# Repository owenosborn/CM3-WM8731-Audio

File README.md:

# CM3-WM8731-Audio
A basic audio board based on Raspberry Pi CM3 and WM8731 audio codec. Eagle PCB files.

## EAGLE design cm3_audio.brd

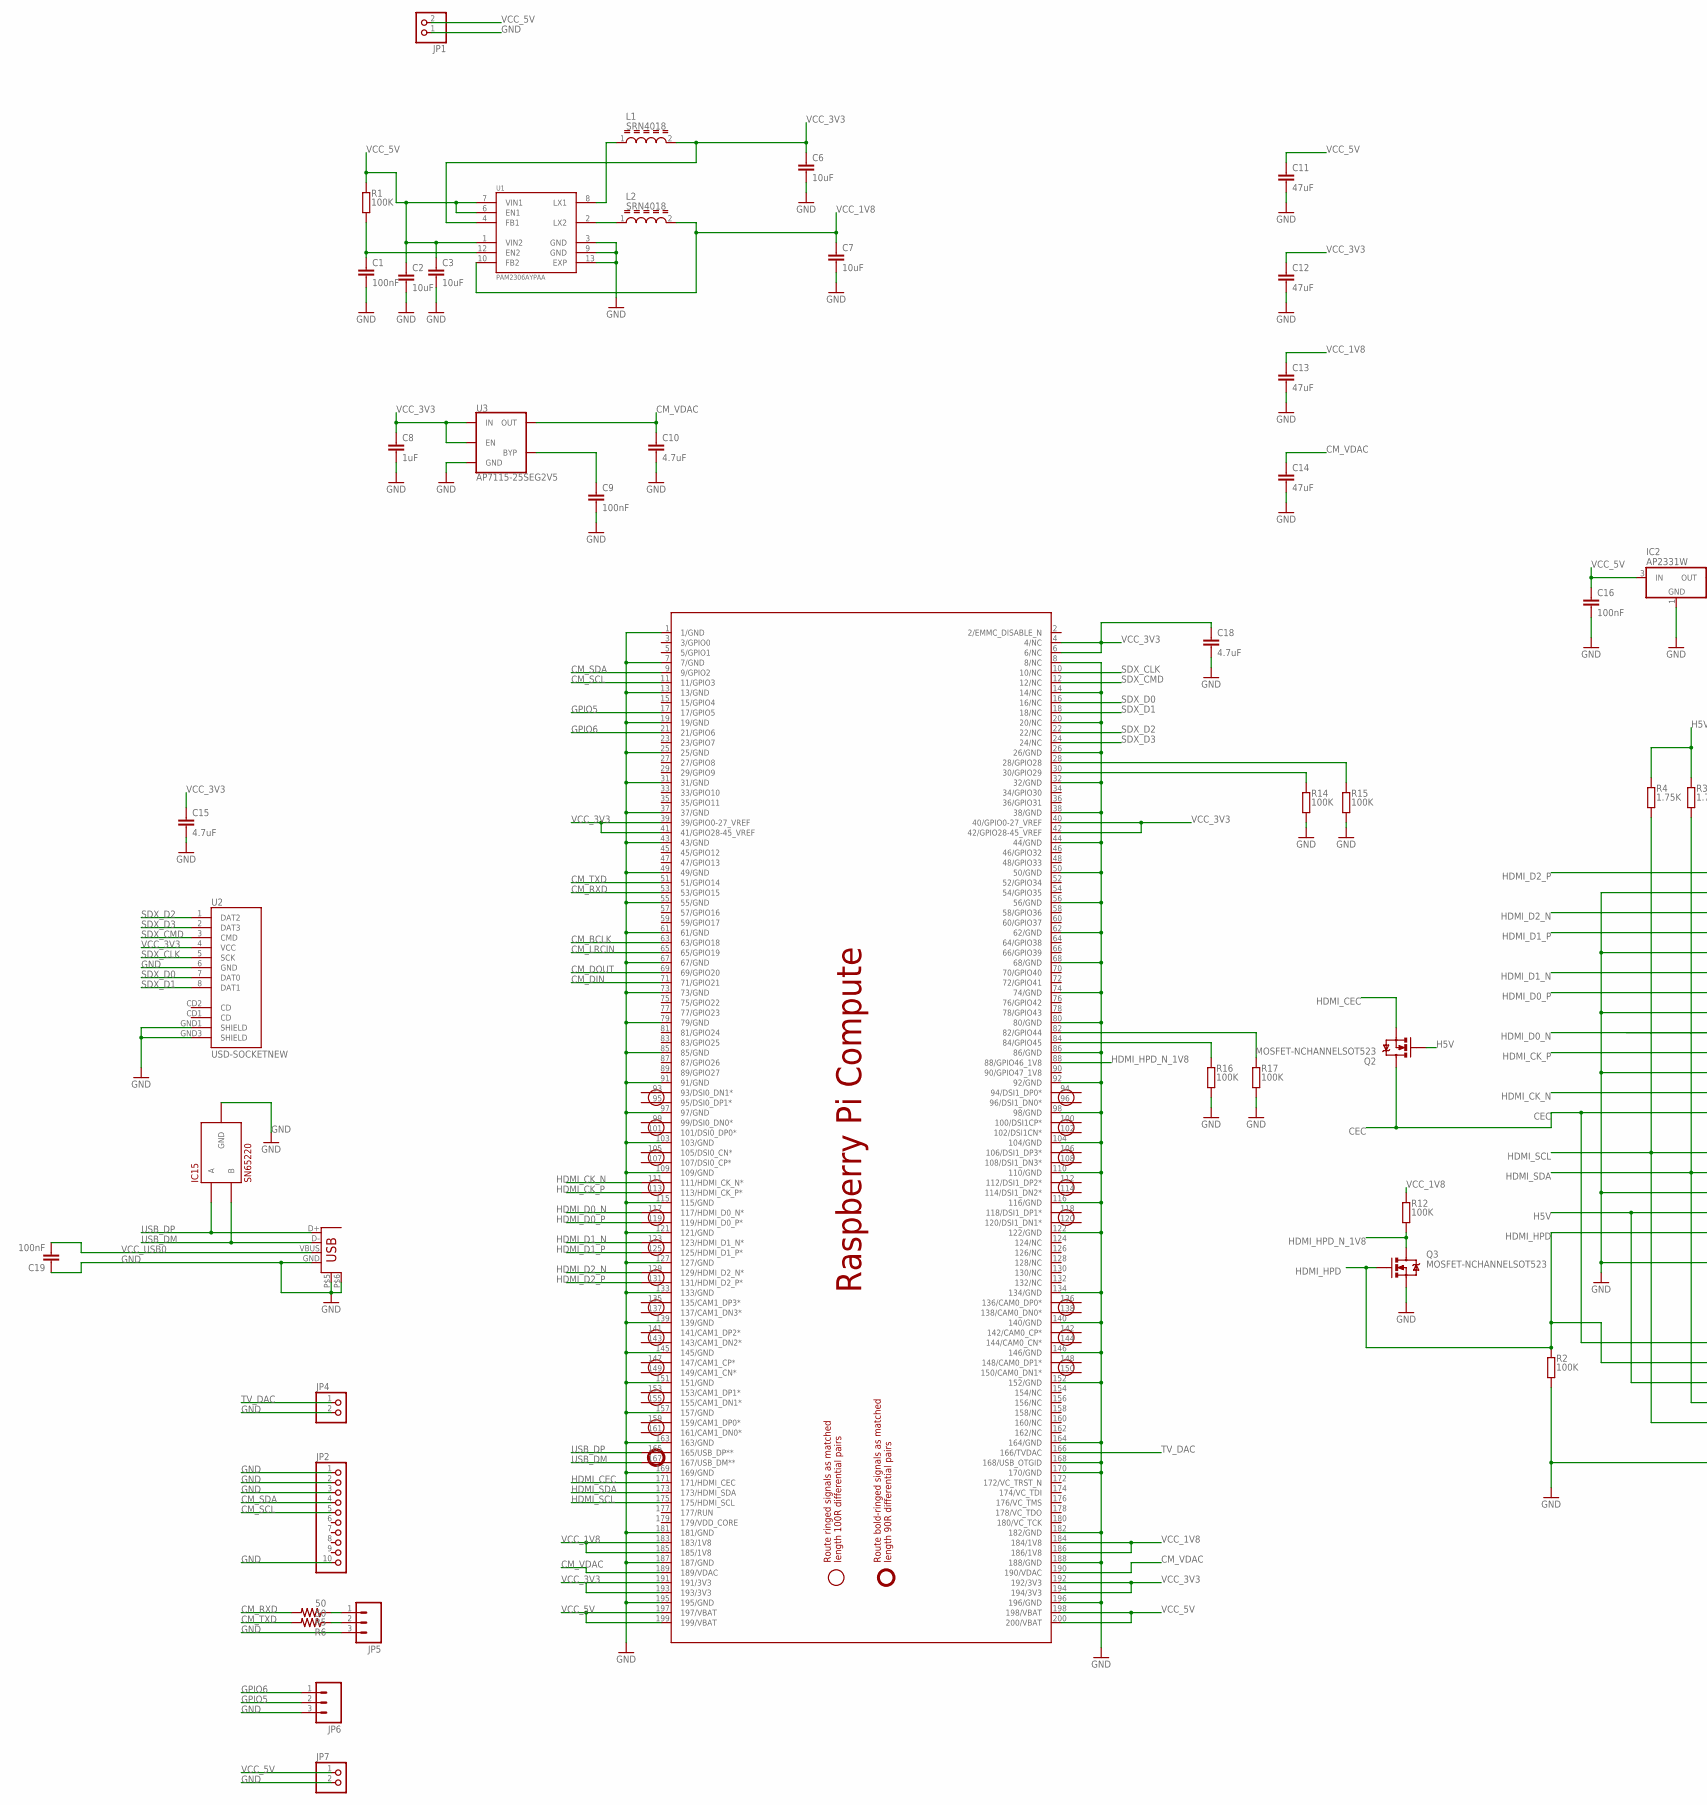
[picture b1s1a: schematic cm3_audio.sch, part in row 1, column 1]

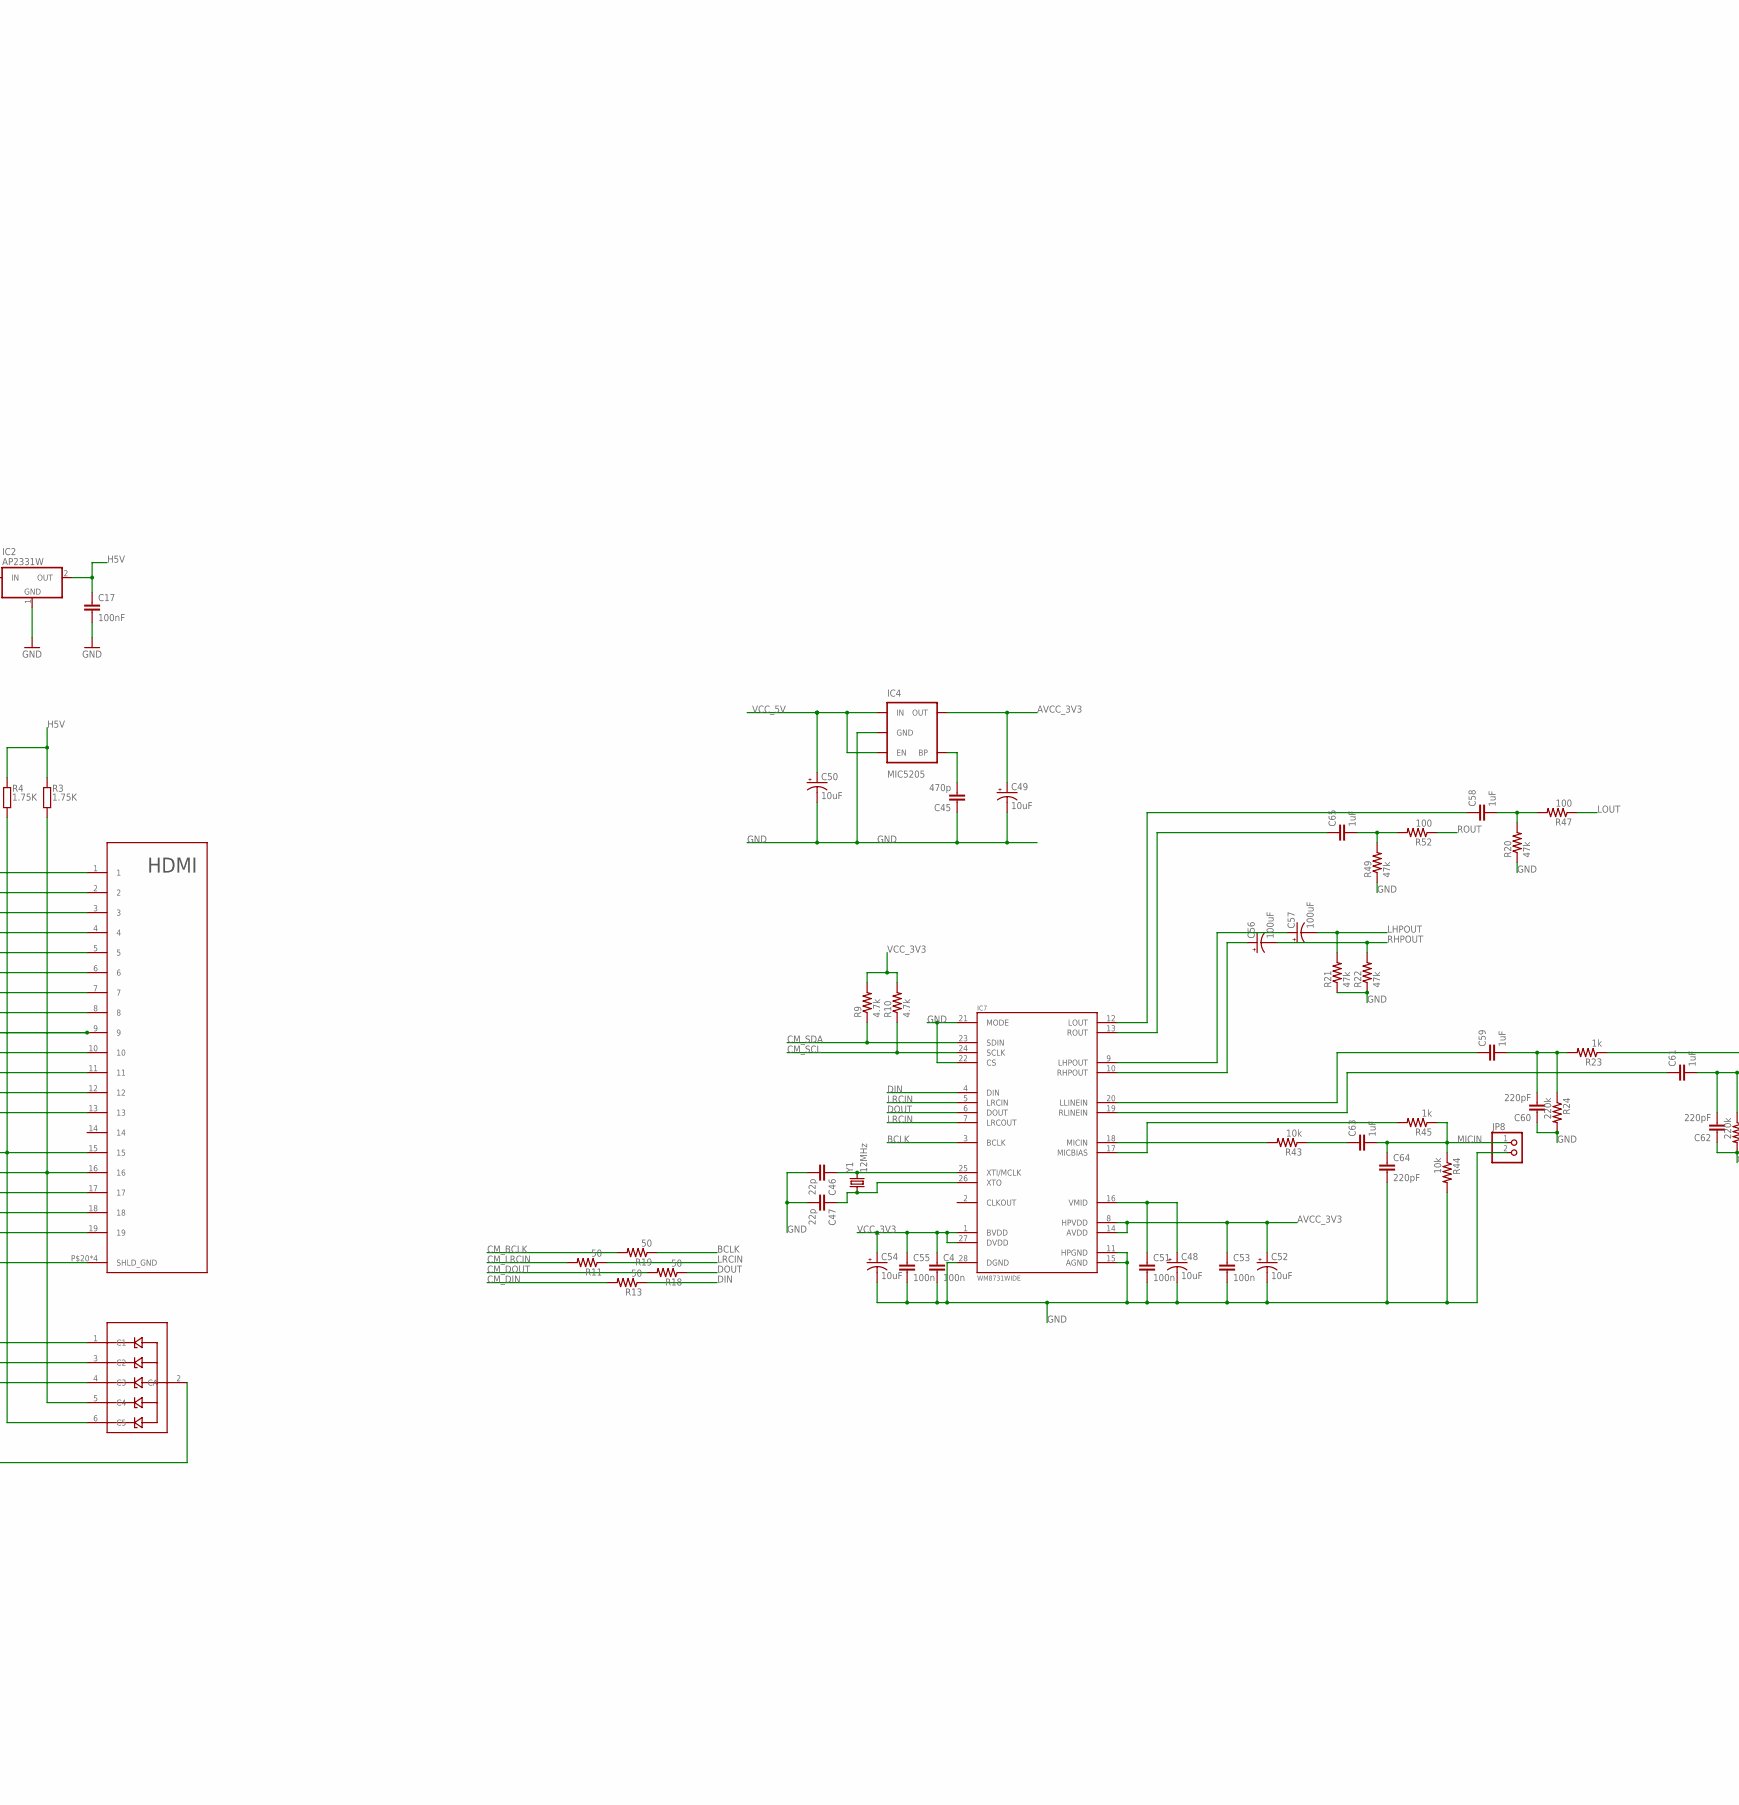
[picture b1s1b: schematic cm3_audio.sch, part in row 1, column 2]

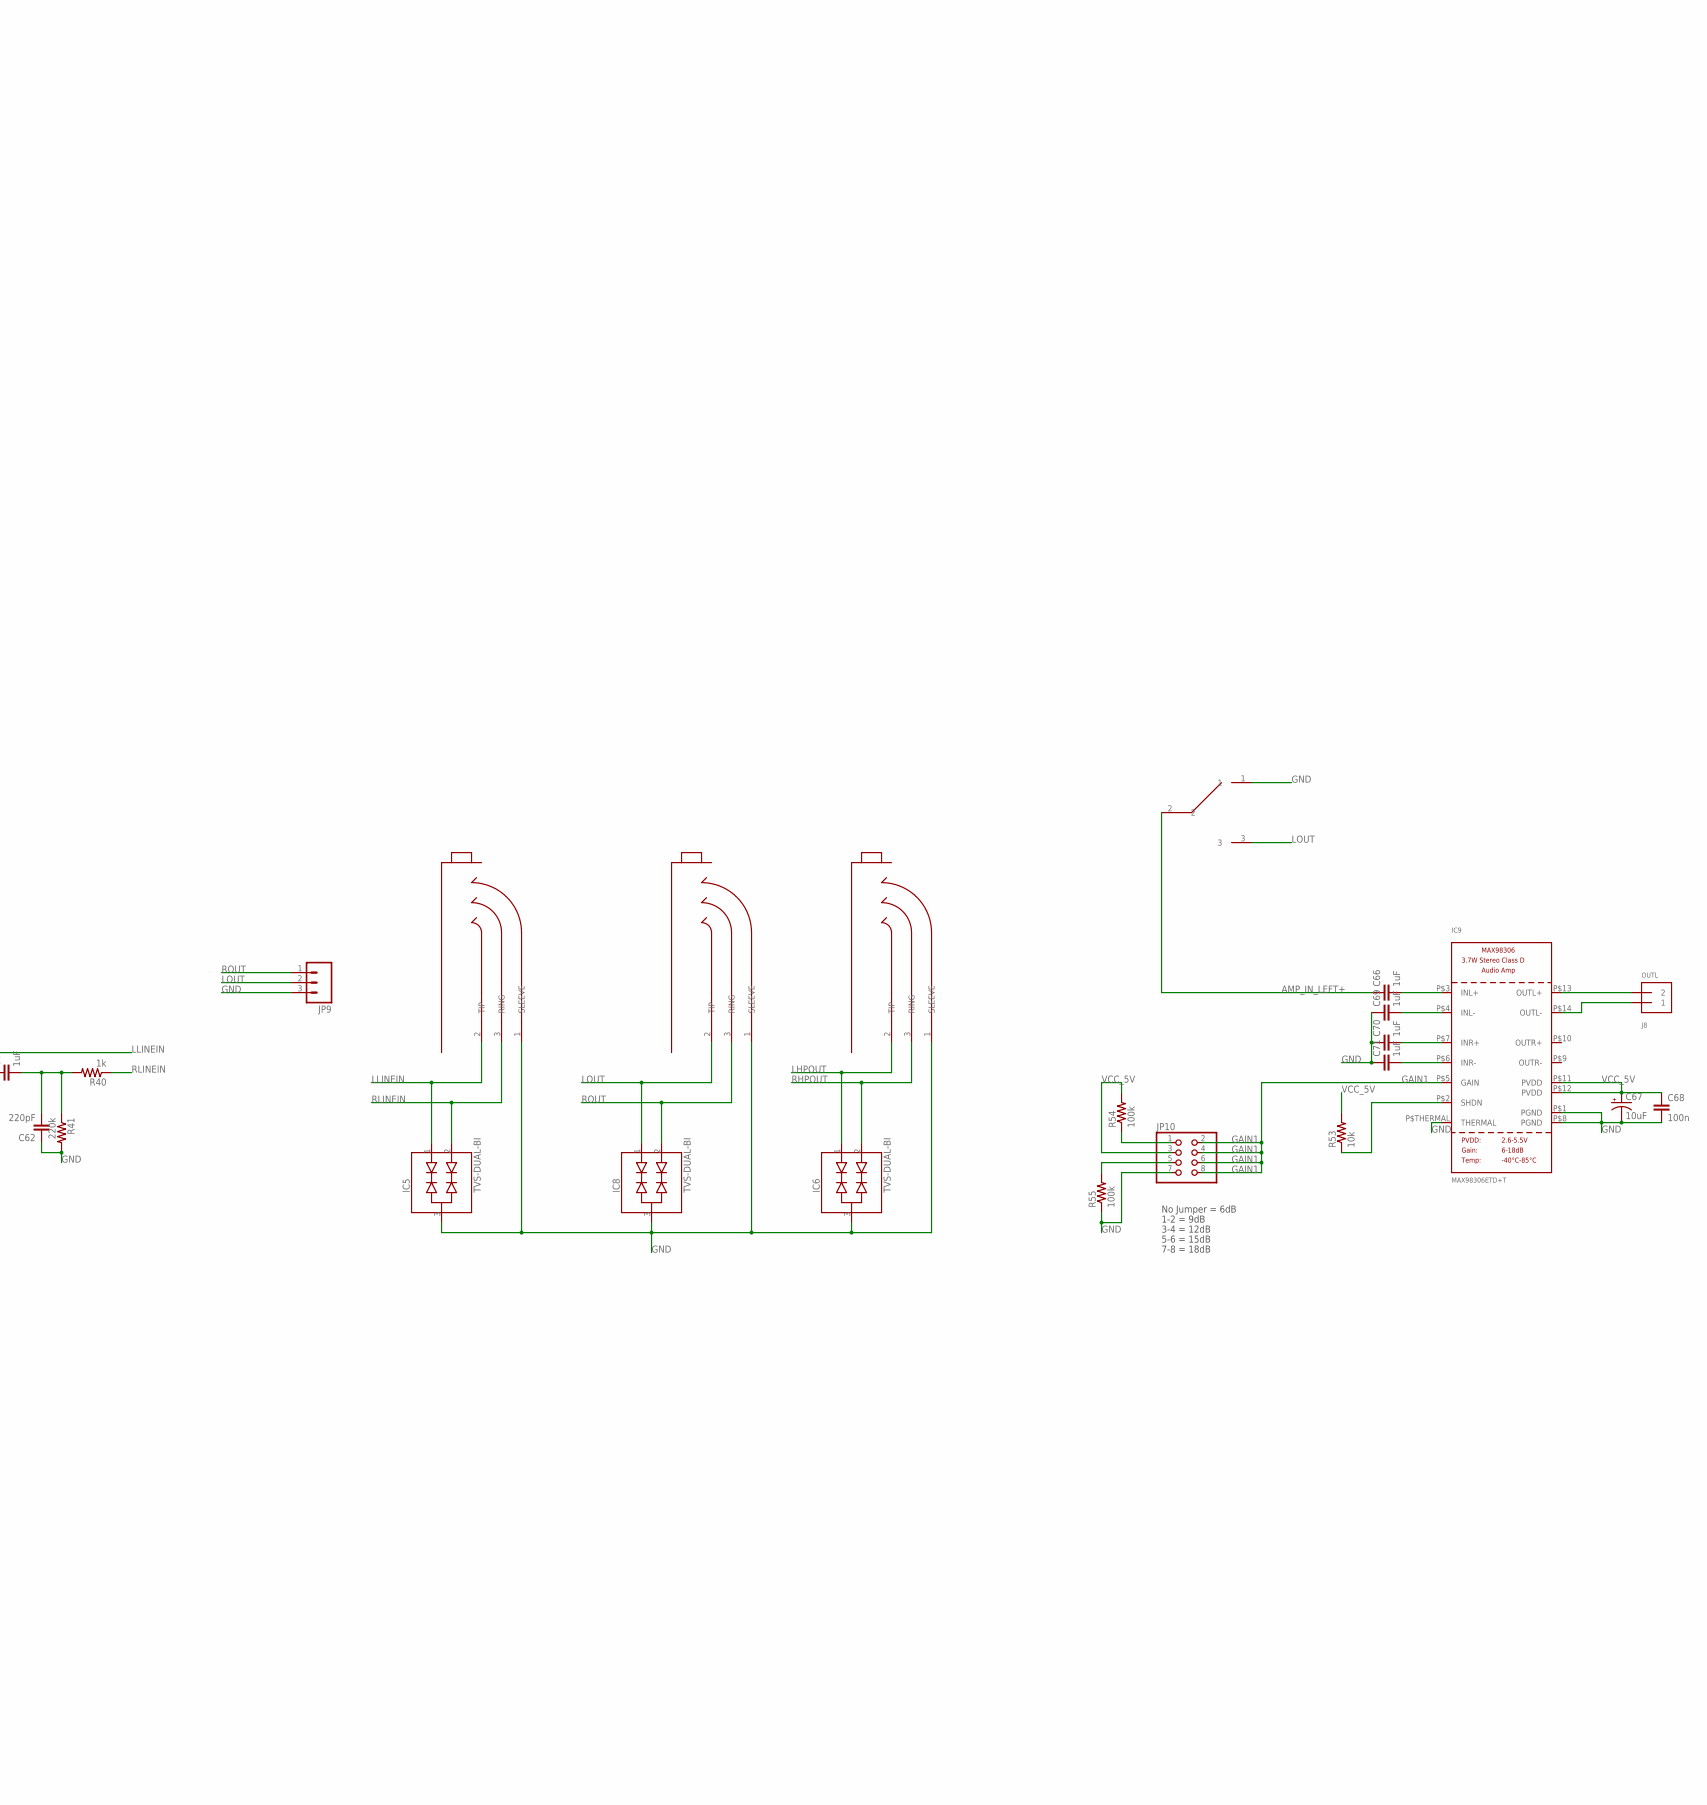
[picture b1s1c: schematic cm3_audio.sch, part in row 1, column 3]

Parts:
C1, C9, C16, C17: 100nF; C0603
C2, C3, C6, C7: 10uF; C0805
C4, C51, C53, C55, C68: 100n; 0603-CAP
C8: 1uF; C0603
C10, C15: 4.7uF; C0603
C11, C12, C13, C14: 47uF; C3216
C18: 4.7uF; C1608
C19: 100nF; 0603-CAP
C45: 470p; 0603-CAP
C46, C47: 22p; 0603-CAP
C48, C49, C50, C52, C54, C67: 10uF; PANASONIC_B
C56, C57: 100uF; PANASONIC_D
C58, C59, C61, C63, C65, C66, C69, C70, C71: 1uF; 0603-CAP
C60, C62, C64: 220pF; 0603-CAP
IC1: PESD3V3L5UYSOT363; SOT363-INFINION
IC2: AP2331W; SOT23
IC4: MIC5205; SPARKFUN-3-2-07_SOT23-5
IC5, IC6, IC8: TVS-DUAL-BI; SOT23
IC7: WM8731WIDE; SSOP28DB
IC9: MAX98306ETD+T; TDFN14_3X3MM
IC15: SN65220; SOT23-6L
J1, J6, J7: STEREO_HEADPHONE_NO_SWITCH; 3.5MM-JACK-SJ1-351X-SMT
J8: OUTL; TERMBLOCK_1X2-3.5MM
JP1, JP4, JP7, JP8: PINHD-1X2; 1X02
JP2: PINHD-1X10; 1X10
JP3: USB-A; USB-A-S-NOSILK-FEMALE
JP5, JP6: M03LOCK_LONGPADS; 1X03_LOCK_LONGPADS
JP9: M03LONGPADS; 1X03_LONGPADS
JP10: PINHD-2X4; 2X04
L1, L2: SRN4018; INDP4040X180N
Q2, Q3: MOSFET-NCHANNELSOT523; SOT523
R1, R2, R12, R14, R15, R16, R17: 100K; R0603
R3, R4: 1.75K; R0603
R5, R6, R11, R13, R18, R19: 50; 0603-RES
R9, R10: 4.7k; 0603-RES
R20, R21, R22, R49: 47k; 0603-RES
R23, R40, R45: 1k; 0603-RES
R24, R41: 220k; 0603-RES
R43, R44, R53: 10k; 0603-RES
R47, R52: 100; 0603-RES
R54, R55: 100k; 0603-RES
S1: SWITCH_SPDTRA; SLIDE_SWITCH_TE_RA
SODIMM: RPI_COMPUTE
U1: PAM2306AYPAA; SON45P300X300X80-13N
U2: USD-SOCKETNEW; MICRO-SD-SOCKET-PP
U3: AP7115-25SEG2V5; SC70
U4: HDMI
Y1: 12MHz; CRYSTAL-SMD-5X3

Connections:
AMP_IN_LEFT+: C66.1, S1.2
AVCC_3V3: C49.+, C52.+, C53.1, IC4.5 (OUT), IC7.8 (HPVDD), IC7.14 (AVDD)
BCLK: IC7.3 (BCLK), R19.1
CEC: IC1.1 (C1), Q2.3 (D), U4.13
CM_BCLK: R19.2, SODIMM.63 (63/GPIO18)
CM_DIN: R13.2, SODIMM.71 (71/GPIO21)
CM_DOUT: R18.2, SODIMM.69 (69/GPIO20)
CM_LRCIN: R11.2, SODIMM.65 (65/GPIO19)
CM_RXD: R5.2, SODIMM.53 (53/GPIO15)
CM_SCL: IC7.24 (SCLK), JP2.5, R10.1, SODIMM.11 (11/GPIO3)
CM_SDA: IC7.23 (SDIN), JP2.4, R9.1, SODIMM.9 (9/GPIO2)
CM_TXD: R6.2, SODIMM.51 (51/GPIO14)
CM_VDAC: C10.1, C14.1, SODIMM.189 (189/VDAC), SODIMM.190 (190/VDAC), U3.5 (OUT)
DIN: IC7.4 (DIN), R13.1
DOUT: IC7.6 (DOUT), R18.1
GAIN1: IC9.P$5 (GAIN), JP10.2, JP10.4, JP10.6, JP10.8
GND: C1.2, C2.2, C3.2, C4.2, C6.2, C7.2, C8.2, C9.2, C10.2, C11.2, C12.2, C13.2, C14.2, C15.2, C16.2, C17.2, C18.2, C19.1, C45.1, C46.2, C47.2, C48.-, C49.-, C50.-, C51.2, C52.-, C53.2, C54.-, C55.2, C60.1, C62.1, C64.2, C67.-, C68.2, C69.1, C70.1, C71.1, IC1.2 (CA), IC2.1 (GND), IC4.2 (GND), IC5.3 (GND), IC6.3 (GND), IC7.11 (HPGND), IC7.15 (AGND), IC7.21 (MODE), IC7.22 (CS), IC7.28 (DGND), IC8.3 (GND), IC9.P$1 (PGND), IC9.P$8 (PGND), IC9.P$THERMAL (THERMAL), IC15.2 (GND), IC15.5 (GND), J1.1 (SLEEVE), J6.1 (SLEEVE), J7.1 (SLEEVE), JP1.1, JP2.1, JP2.2, JP2.3, JP2.10, JP3.GND, JP3.P$5 (SHIELD1), JP3.P$6 (SHIELD2), JP4.2, JP5.3, JP6.3, JP7.2, JP8.2, JP9.3, JP10.7, Q3.2 (S), R2.1, R14.1, R15.1, R16.1, R17.1, R20.1, R21.1, R22.1, R24.2, R41.2, R44.2, R49.1, R55.1, S1.1, SODIMM.1 (1/GND), SODIMM.7 (7/GND), SODIMM.8 (8/NC), SODIMM.13 (13/GND), SODIMM.14 (14/NC), SODIMM.19 (19/GND), SODIMM.20 (20/NC), SODIMM.25 (25/GND), SODIMM.26 (26/GND), SODIMM.31 (31/GND), SODIMM.32 (32/GND), SODIMM.37 (37/GND), SODIMM.38 (38/GND), SODIMM.43 (43/GND), SODIMM.44 (44/GND), SODIMM.49 (49/GND), SODIMM.50 (50/GND), SODIMM.55 (55/GND), SODIMM.56 (56/GND), SODIMM.61 (61/GND), SODIMM.62 (62/GND), SODIMM.67 (67/GND), SODIMM.68 (68/GND), SODIMM.73 (73/GND), SODIMM.74 (74/GND), SODIMM.79 (79/GND), SODIMM.80 (80/GND), SODIMM.85 (85/GND), SODIMM.86 (86/GND), SODIMM.91 (91/GND), SODIMM.92 (92/GND), SODIMM.97 (97/GND), SODIMM.98 (98/GND), SODIMM.103 (103/GND), SODIMM.104 (104/GND), SODIMM.109 (109/GND), SODIMM.110 (110/GND), SODIMM.115 (115/GND), SODIMM.116 (116/GND), SODIMM.121 (121/GND), SODIMM.122 (122/GND), SODIMM.127 (127/GND), SODIMM.133 (133/GND), SODIMM.134 (134/GND), SODIMM.139 (139/GND), SODIMM.140 (140/GND), SODIMM.145 (145/GND), SODIMM.146 (146/GND), SODIMM.151 (151/GND), SODIMM.152 (152/GND), SODIMM.157 (157/GND), SODIMM.163 (163/GND), SODIMM.164 (164/GND), SODIMM.168 (168/USB_OTGID), SODIMM.169 (169/GND), SODIMM.170 (170/GND), SODIMM.181 (181/GND), SODIMM.182 (182/GND), SODIMM.187 (187/GND), SODIMM.188 (188/GND), SODIMM.195 (195/GND), SODIMM.196 (196/GND), U1.3 (GND), U1.9 (GND), U1.13 (EXP), U2.6 (GND), U2.GND1 (SHIELD), U2.GND3 (SHIELD), U3.2 (GND), U4.2, U4.5, U4.8, U4.11, U4.17, U4.P$20 (SHLD_GND), U4.P$21 (SHLD_GND), U4.P$22 (SHLD_GND), U4.P$23 (SHLD_GND)
GPIO5: JP6.2, SODIMM.17 (17/GPIO5)
GPIO6: JP6.1, SODIMM.21 (21/GPIO6)
H5V: C17.1, IC1.4 (C3), IC2.2 (OUT), Q2.1 (G), R3.2, R4.2, U4.18
HDMI_CEC: Q2.2 (S), SODIMM.171 (171/HDMI_CEC)
HDMI_CK_N: SODIMM.111 (111/HDMI_CK_N*), U4.12
HDMI_CK_P: SODIMM.113 (113/HDMI_CK_P*), U4.10
HDMI_D0_N: SODIMM.117 (117/HDMI_D0_N*), U4.9
HDMI_D0_P: SODIMM.119 (119/HDMI_D0_P*), U4.7
HDMI_D1_N: SODIMM.123 (123/HDMI_D1_N*), U4.6
HDMI_D1_P: SODIMM.125 (125/HDMI_D1_P*), U4.4
HDMI_D2_N: SODIMM.129 (129/HDMI_D2_N*), U4.3
HDMI_D2_P: SODIMM.131 (131/HDMI_D2_P*), U4.1
HDMI_HPD: IC1.3 (C2), Q3.1 (G), R2.2, U4.19
HDMI_HPD_N_1V8: Q3.3 (D), R12.1, SODIMM.88 (88/GPIO46_1V8)
HDMI_SCL: IC1.6 (C5), R4.1, SODIMM.175 (175/HDMI_SCL), U4.15
HDMI_SDA: IC1.5 (C4), R3.1, SODIMM.173 (173/HDMI_SDA), U4.16
LHPOUT: C57.-, IC6.1 (IO1), J1.2 (TIP), R21.2
LLINEIN: IC5.1 (IO1), J7.2 (TIP), R23.1
LOUT: IC8.1 (IO1), J6.2 (TIP), JP9.2, R47.1, S1.3
LOUT-1: IC9.P$14 (OUTL-), J8.1
LRCIN: IC7.5 (LRCIN), IC7.7 (LRCOUT), R11.1
MICIN: C63.2, C64.1, JP8.1, R44.1, R45.1
unnamed: L1.1, U1.8 (LX1)
unnamed: C1.1, R1.1, U1.12 (EN2)
unnamed: JP5.1, R5.1
unnamed: JP5.2, R6.1
unnamed: L2.1, U1.2 (LX2)
unnamed: C9.1, U3.4 (BYP)
unnamed: R16.2, SODIMM.84 (84/GPIO45)
unnamed: R15.2, SODIMM.28 (28/GPIO28)
unnamed: R14.2, SODIMM.30 (30/GPIO29)
unnamed: R17.2, SODIMM.82 (82/GPIO44)
unnamed: C45.2, IC4.4 (BP)
unnamed: C46.1, IC7.25 (XTI/MCLK), Y1.3 (2)
unnamed: C47.1, IC7.26 (XTO), Y1.1
unnamed: C48.+, C51.1, IC7.16 (VMID)
unnamed: C59.2, C60.2, R23.2, R24.1
unnamed: C58.1, IC7.12 (LOUT)
unnamed: C57.+, IC7.9 (LHPOUT)
unnamed: C56.+, IC7.10 (RHPOUT)
unnamed: C61.2, C62.2, R40.2, R41.1
unnamed: C59.1, IC7.20 (LLINEIN)
unnamed: C61.1, IC7.19 (RLINEIN)
unnamed: IC7.18 (MICIN), R43.2
unnamed: C63.1, R43.1
unnamed: IC7.17 (MICBIAS), R45.2
unnamed: C58.2, R20.2, R47.2
unnamed: C65.2, R49.2, R52.2
unnamed: C65.1, IC7.13 (ROUT)
unnamed: JP10.1, R54.1
unnamed: JP10.5, R55.2
unnamed: C66.2, IC9.P$3 (INL+)
unnamed: IC9.P$13 (OUTL+), J8.2
unnamed: IC9.P$2 (SHDN), R53.1
unnamed: C69.2, IC9.P$4 (INL-)
unnamed: C70.2, IC9.P$7 (INR+)
unnamed: C71.2, IC9.P$6 (INR-)
RHPOUT: C56.-, IC6.2 (IO2), J1.3 (RING), R22.2
RLINEIN: IC5.2 (IO2), J7.3 (RING), R40.1
ROUT: IC8.2 (IO2), J6.3 (RING), JP9.1, R52.1
SDX_CLK: SODIMM.10 (10/NC), U2.5 (SCK)
SDX_CMD: SODIMM.12 (12/NC), U2.3 (CMD)
SDX_D0: SODIMM.16 (16/NC), U2.7 (DAT0)
SDX_D1: SODIMM.18 (18/NC), U2.8 (DAT1)
SDX_D2: SODIMM.22 (22/NC), U2.1 (DAT2)
SDX_D3: SODIMM.24 (24/NC), U2.2 (DAT3)
TV_DAC: JP4.1, SODIMM.166 (166/TVDAC)
USB_DM: IC15.4 (B), JP3.D-, SODIMM.167 (167/USB_DM**)
USB_DP: IC15.6 (A), JP3.D+, SODIMM.165 (165/USB_DP**)
VCC_1V8: C7.1, C13.1, L2.2, R12.2, SODIMM.183 (183/1V8), SODIMM.184 (184/1V8), SODIMM.185 (185/1V8), SODIMM.186 (186/1V8), U1.10 (FB2)
VCC_3V3: C4.1, C6.1, C8.1, C12.1, C15.1, C18.1, C54.+, C55.1, IC7.1 (BVDD), IC7.27 (DVDD), L1.2, R9.2, R10.2, SODIMM.4 (4/NC), SODIMM.6 (6/NC), SODIMM.39 (39/GPIO0-27_VREF), SODIMM.40 (40/GPIO0-27_VREF), SODIMM.41 (41/GPIO28-45_VREF), SODIMM.42 (42/GPIO28-45_VREF), SODIMM.191 (191/3V3), SODIMM.192 (192/3V3), SODIMM.193 (193/3V3), SODIMM.194 (194/3V3), U1.4 (FB1), U2.4 (VCC), U3.1 (IN), U3.3 (EN)
VCC_5V: C2.1, C3.1, C11.1, C16.1, C50.+, C67.+, C68.1, IC2.3 (IN), IC4.1 (IN), IC4.3 (EN), IC9.P$11 (PVDD), IC9.P$12 (PVDD), JP1.2, JP7.1, JP10.3, R1.2, R53.2, R54.2, SODIMM.197 (197/VBAT), SODIMM.198 (198/VBAT), SODIMM.199 (199/VBAT), SODIMM.200 (200/VBAT), U1.1 (VIN2), U1.6 (EN1), U1.7 (VIN1)
VCC_USB0: C19.2, JP3.VBUS

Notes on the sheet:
No Jumper = 6dB
1-2 = 9dB
3-4 = 12dB
5-6 = 15dB
7-8 = 18dB

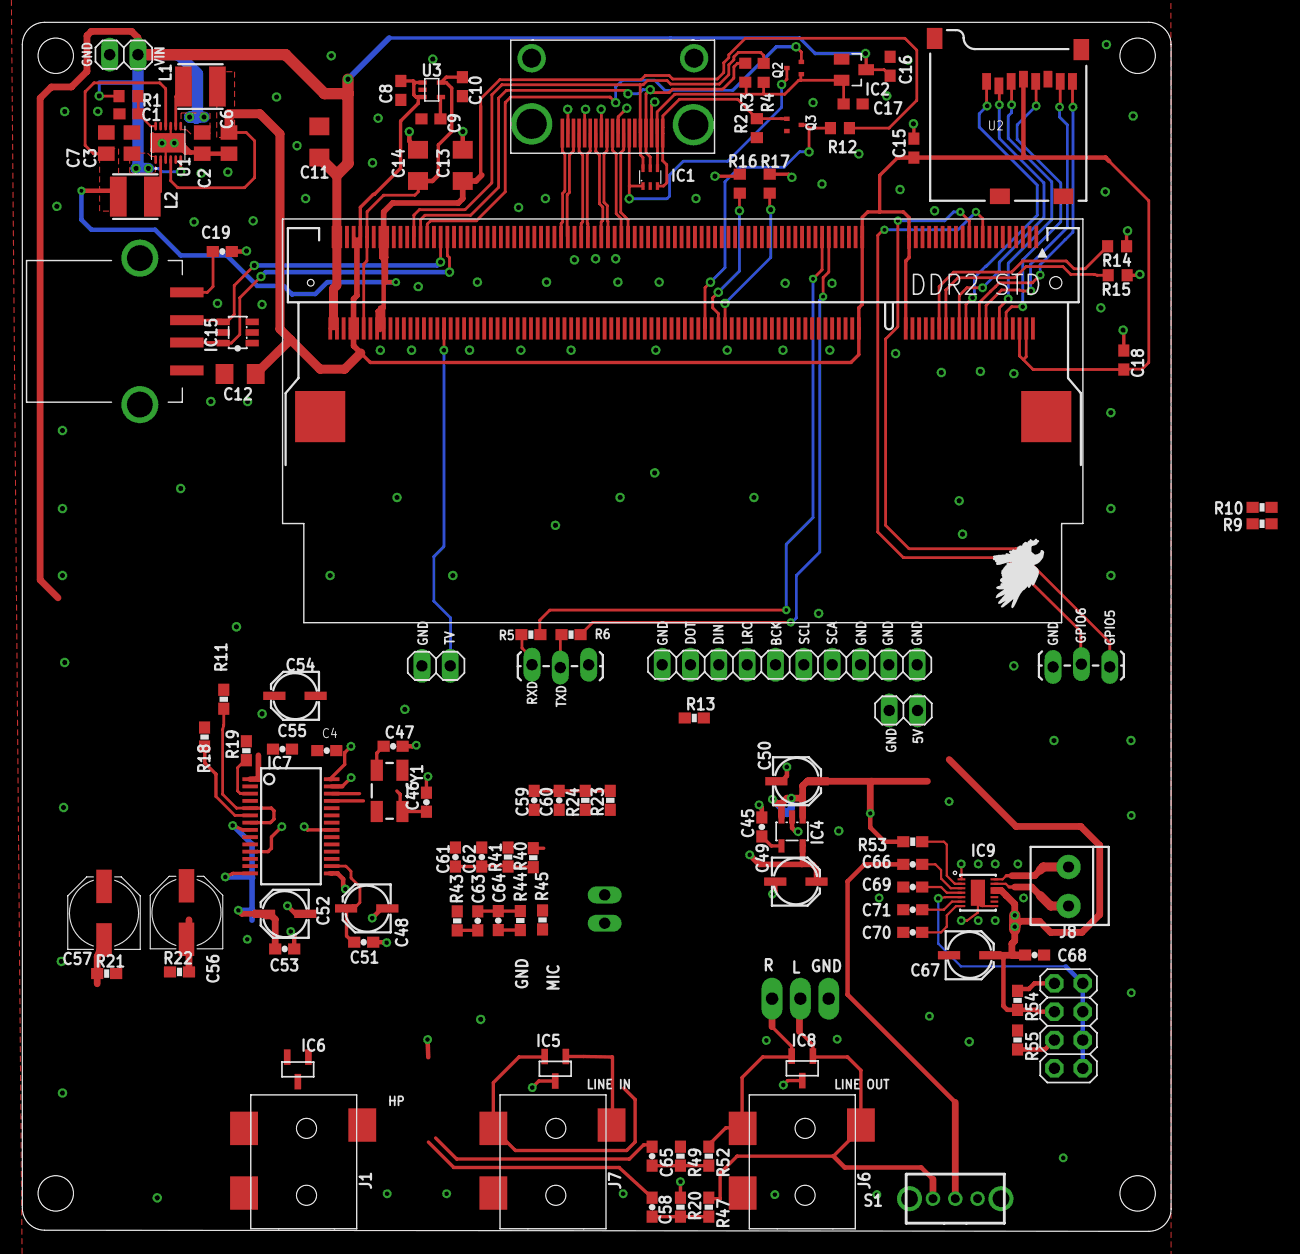
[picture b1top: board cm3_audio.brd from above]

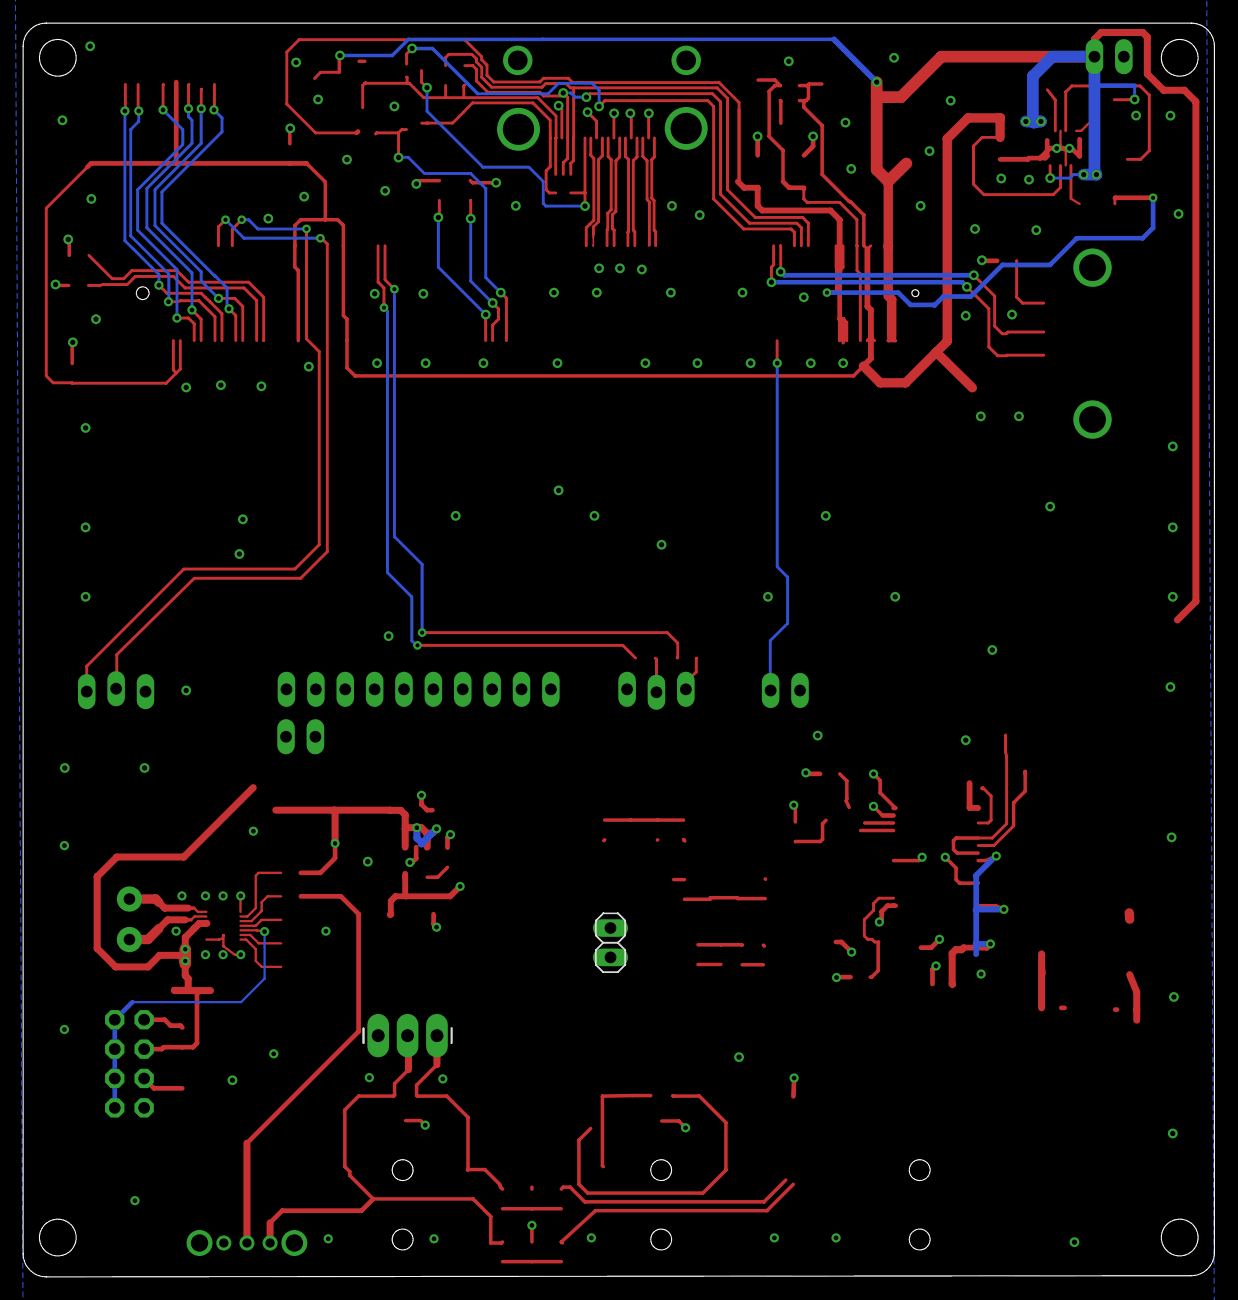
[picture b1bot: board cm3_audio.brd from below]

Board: 4 copper layers, 103.0 x 108.4 mm, 112 parts (2 on the bottom side), 90 nets.

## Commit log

2018-09-25 adding files
2018-09-25 adding schematic image
2018-10-03 fixing codec layout
